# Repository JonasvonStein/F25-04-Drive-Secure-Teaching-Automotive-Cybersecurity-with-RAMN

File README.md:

F25-04: Drive Secure Teaching Automotive Cybersecurity with RAMN
=======================================

This GitHub lays out the fundamentals for automotive cybersecurity utilizing RAMN.

To view the cybersecurity challenges, view the `Challenges folder <https://github.com/JonasvonStein/F25-04-Drive-Secure-Teaching-Automotive-Cybersecurity-with-RAMN/tree/main/Challenges>`_

To access the hints to each challenge access `hints <https://github.com/JonasvonStein/F25-04-Drive-Secure-Teaching-Automotive-Cybersecurity-with-RAMN/tree/main/docs/challengeHints>`_

To access our other documentation about CAN, UDS, RAMN, CARLA click `here <https://github.com/JonasvonStein/F25-04-Drive-Secure-Teaching-Automotive-Cybersecurity-with-RAMN/tree/main/Documentation>`_

Visit our Website `here <https://f25-04-drive-secure-teaching-automotive-cybersecurity-with-ramn.readthedocs.io/en/latest/index.html>`_

.. image:: Images/Team Picture.png
       :alt: F25-04 Team Photo
       :align: center

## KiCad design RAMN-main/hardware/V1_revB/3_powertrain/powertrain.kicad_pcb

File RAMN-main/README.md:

# RAMN

RAMN (Resistant Automotive Miniature Network) is a miniature CAN/CAN-FD testbed of four Electronic Control Units (ECUs) consiting solely of Printed Circuit Boards. The ECUs can be programmed to emulate the same network traffic as [PASTA](https://github.com/pasta-auto/PASTA1.0), another project from our team. RAMN is powered over USB and can be recognized as a standard CAN adapter. It can be connected in closed-loop with the autonomous driving simulator [CARLA](https://github.com/carla-simulator/carla). What happens to the virtual vehicle has an impact on the physical CAN/CAN-FD bus, and vice versa. RAMN can be expanded with many stackable expansions, ranging from external quadSPI memories to Trusted Platform Modules (TPMs).

Please check the [Documentation](https://ramn.readthedocs.io/) for demonstrations and details.

 [^1]

[^1]: pointing temporarily at a fork while this org's policies prevent automated builds)

## Fabricating RAMN boards

This project is open-source and RAMN boards can be fabricated by most PCB assembly prototyping services.

We have setup 're-orders' at PCBWay. 
Please [see the docs 'PCB Ordering' for more details](https://ramn.readthedocs.io/page/hardware/Fabrication/ordering.html).
You can also request a prototype from any PCB manufacturer, using the Gerber files and BOM in the Hardware folder. 

Feel free to [contact RAMN Creator at Toyota](mailto:camille.gay@toyota.global) if you need assistance to fabricate or sell RAMN boards.

Because component availability is subject to change, we are periodically updating the hardware.
The original RAMN hardware data is available in misc/RAMN_V1_reference_PCB.zip, and is recommended for academic purposes.

## Project structure
### Hardware folder
Contains design files, from KiCAD project files to Gerber files and BOM.

### Scripts folder

Contains various scripts to interact with the ECUs:
- Driving Simulator
- Diagnostics (UDS/KWP2000/XCP)
- Hardware Bootloader
- Connection to a virtual CAN Network

### Firmware folder
Contains firmware source code for RAMN's ECUs.

## License
Please check the LICENSE.md file for more details.

## Contact
Feel free to [contact RAMN creator at Toyota](mailto:camille.gay@toyota.global) if you have questions.
Videos available [here](https://twitter.com/ramn_auto).

Copyright (c) 2025 TOYOTA MOTOR CORPORATION. ALL RIGHTS RESERVED.

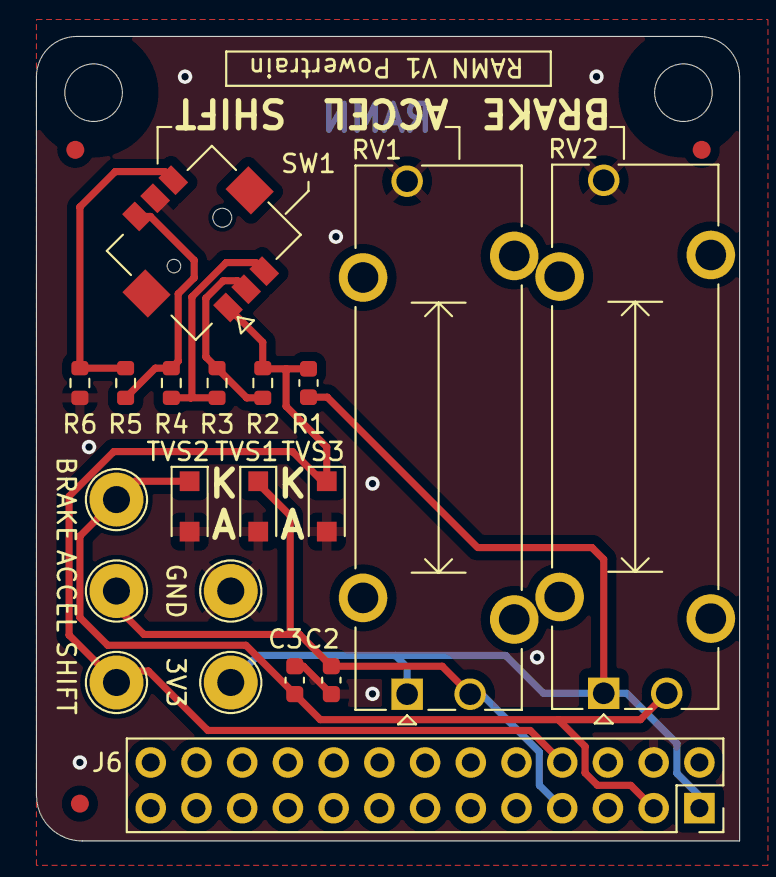
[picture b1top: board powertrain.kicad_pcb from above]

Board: 2 copper layers, 39.1 x 44.7 mm, 25 parts (0 on the bottom side), 9 nets.

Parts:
3V3: TestPoint; TestPoint_Loop_D2.54mm_Drill1.5mm_Beaded
ACCEL: TestPoint; TestPoint_Loop_D2.54mm_Drill1.5mm_Beaded
BRAKE: TestPoint; TestPoint_Loop_D2.54mm_Drill1.5mm_Beaded
C2, C3: 100nF; C_0603_1608Metric
FID1, FID2, FID3: Fiducial; Fiducial_1mm_Mask2mm
GND: TestPoint; TestPoint_Loop_D2.54mm_Drill1.5mm_Beaded
H1, H2: MountingHole; MountingHole_3.2mm_M3_ISO7380
J6: PinSocket_2x13_P2.54mm_Vertical
R1, R2, R3, R4, R5, R6: 10k; R_0603_1608Metric
RV1, RV2: R_POT_TRIM_US; Potentiometer_Bourns_PTA1543_Single_Slide
SHIFT: TestPoint; TestPoint_Loop_D2.54mm_Drill1.5mm_Beaded
SW1: SKRHADE010
TVS1, TVS2, TVS3: D_TVS; D_SOD-123F

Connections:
/3V3_ECU: 3V3.1, J6.1, R1.1, RV1.1, RV2.1
Accel: ACCEL.1, C2.1, J6.7, RV1.2, TVS1.1
Brake: BRAKE.1, C3.1, J6.3, RV2.2, TVS2.1
GND: C2.2, C3.2, GND.1, J6.4, R6.2, RV1.3, RV2.3, SW1.5, TVS1.2, TVS2.2, TVS3.2
JOYSTICK: J6.8, R1.2, R2.1, SHIFT.1, SW1.1, TVS3.1
unnamed: R2.2, R3.1, SW1.2
unnamed: R3.2, R4.1, SW1.3
unnamed: R4.2, R5.1, SW1.4
unnamed: R5.2, R6.1, SW1.6

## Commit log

2025-10-16 Trying ReadTheDocs
    Trying ReadTheDocs
2025-10-16 Trying to add new page
    Trying to add new page
2025-10-22 Added RAMN repo
2025-10-22 updated the home page
2025-10-22 added intro
2025-10-22 fixing intro?
2025-10-22 add VTTI image
2025-10-22 Fix image and intro
2025-10-22 Update image
2025-10-22 fixed Image?
2025-10-22 Fixed Image again?
2025-10-22 Change setup
2025-11-05 added challenges files
2025-11-05 Added formating
2025-11-05 saved all
2025-11-05 fix image?
2025-11-05 trying to add a PDF
2025-11-05 trying more pdf displaying
2025-11-09 fixed intro and add more to it
2025-11-09 adding challenges
2025-11-09 fixed challenge
2025-11-09 Fixed spelling and add more docs
2025-11-09 add challenge Solutions
2025-11-09 Added Hints page
2025-11-09 added how to use page
2025-11-09 fixed homepage
2025-11-10 add brute force
2025-11-10 fixing brute force
2025-11-10 fixing page
2025-11-10 add pictures and addded Capture the flag
2025-11-10 fixed bullet points
2025-11-10 fixed bullet points?
2025-11-10 add pics
2025-11-10 update images and solutions
2025-11-10 fixed image scaling
2025-11-10 added TeraTerm
2025-11-10 trying toggle
2025-11-10 improved formating
2025-11-10 asdasdas
2025-11-10 edits
2025-11-10 fixed title
2025-11-12 Code with missing values for beginners
2025-11-12 Added hints for bruteforce
2025-11-12 Added our bruteforce solution code
2025-11-12 Bruteforce challenge
2025-11-17 Rename README.md to Challenge Intro.md
2025-11-17 Add ecu_control.py
    ecu_control.py commit to project github.
2025-11-17 Add README.md for ECU Manipulatoin
2025-11-17 Add README for Brute Force
    Added an overview of brute force techniques and a challenge description for the USB Challenge, including requirements for creating and running the script.
2025-11-17 Create F25-04 Documentation
    Commit full F25-04 Documentation
2025-11-17 asdasd
2025-11-17 fix ecu man
2025-11-17 upadate
2025-11-17 ecu man
2025-11-17 edit CTF
2025-11-17 aswe
2025-11-17 Create About CAN.rst
    new file about CAN
2025-11-17 Update About CAN.rst
    Update text
2025-11-17 Create About UDS.rst
    initial
2025-11-17 Update About UDS.rst
    update text
2025-11-17 add linux
2025-11-17 Create CARLA on Native Ubuntu.rst
    update text
2025-11-17 Update CARLA on Native Ubuntu.rst
    update text
2025-11-17 Update README.rst
    updated hyperlinks
2025-11-17 added how to
2025-11-17 Update README.rst
    fixed readme
2025-11-18 Create README.md
    images folder
2025-11-18 Add files via upload
    Team photo
2025-11-18 Add files via upload
    team picture
2025-11-18 uds2
2025-11-18 Rename Team Picture.png to Team_Picture.png
2025-11-18 fixes
2025-11-18 Update brute force hints
2025-11-18 added ctf s
2025-11-18 Create Hints
2025-11-18 fix ctf s
2025-11-18 fixed ctf h
2025-11-18 Update Brute_Force_Scripting.rst
    Clarified the explanation of brute forcing in the context of automotive hacking.
2025-11-18 Update CARLA.rst
    Correct capitalization and formatting for consistency and clarity.
2025-11-18 update flash ramn
2025-11-18 Update index.rst
    Corrected capitalization and minor wording adjustments in the introduction.
2025-11-18 Update introduction.rst
    Corrected spelling and punctuation in introduction.
